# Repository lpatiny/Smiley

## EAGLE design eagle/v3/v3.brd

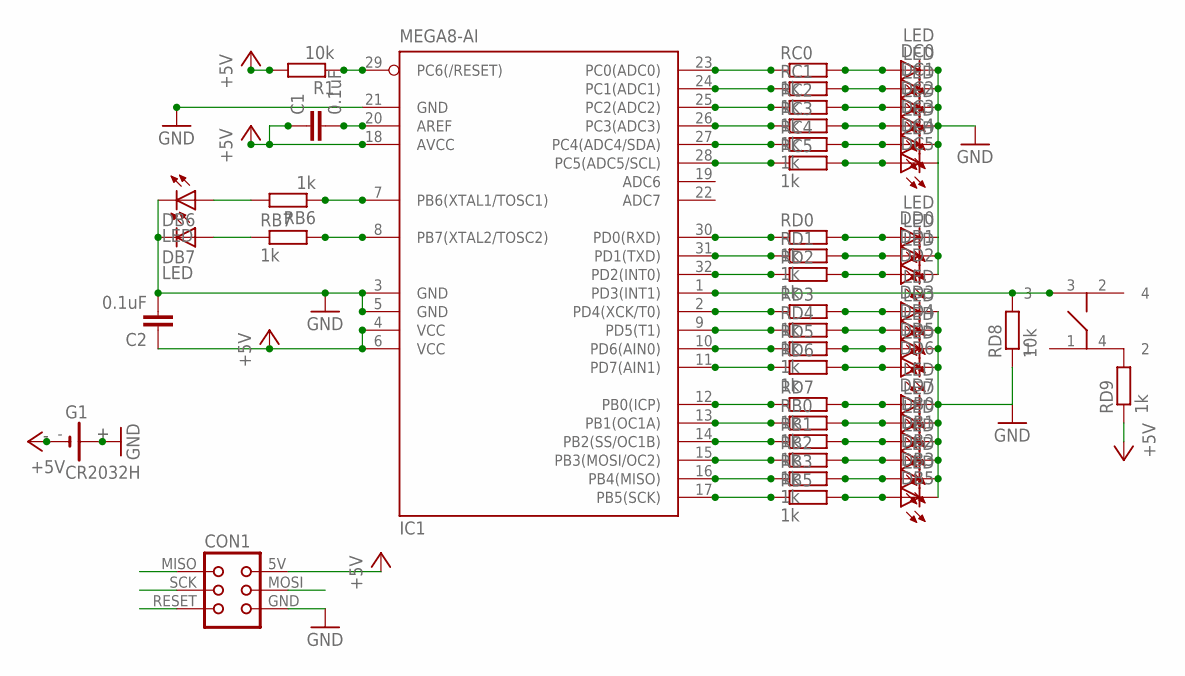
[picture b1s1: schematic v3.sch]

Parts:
C1, C2: 0.1uF; C0402
CON1: TINYISPT; TC2030-MCP-NL
DB0, DB1, DB2, DB3, DB5, DB6, DB7: LED; D0402
DC0, DC1, DC2, DC3, DC4, DC5: LED; D0402
DD0, DD1, DD2, DD3, DD4, DD5, DD6, DD7: LED; D0402
G1: CR2032H
IC1: MEGA8-AI; TQFP32-08
R1: 10k; R0402
RB0, RB1, RB2, RB3, RB5, RB6, RB7: 1k; R0402
RC0, RC1, RC2, RC3, RC4, RC5: 1k; R0402
RD0, RD1, RD2, RD3, RD4, RD5, RD6, RD7, RD9: 1k; R0402
RD8: 10k; R0402
U$2: TEUCH4MM

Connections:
+5V: C1.1, C2.1, CON1.5V (VCC), G1.-, IC1.4 (VCC), IC1.6 (VCC), IC1.18 (AVCC), R1.2, RD9.1
GND: C2.2, CON1.GND, DB0.C, DB1.C, DB2.C, DB3.C, DB5.C, DB6.C, DB7.C, DC0.C, DC1.C, DC2.C, DC3.C, DC4.C, DC5.C, DD0.C, DD1.C, DD2.C, DD3.C, DD4.C, DD5.C, DD6.C, DD7.C, G1.+, IC1.3 (GND), IC1.5 (GND), IC1.21 (GND), RD8.1
MISO: CON1.MISO
MOSI: CON1.MOSI
unnamed: IC1.7 (PB6(XTAL1/TOSC1)), RB6.1
unnamed: IC1.24 (PC1(ADC1)), RC1.1
unnamed: IC1.23 (PC0(ADC0)), RC0.1
unnamed: C1.2, IC1.20 (AREF)
unnamed: IC1.26 (PC3(ADC3)), RC3.1
unnamed: IC1.25 (PC2(ADC2)), RC2.1
unnamed: IC1.27 (PC4(ADC4/SDA)), RC4.1
unnamed: IC1.28 (PC5(ADC5/SCL)), RC5.1
unnamed: IC1.30 (PD0(RXD)), RD0.1
unnamed: IC1.31 (PD1(TXD)), RD1.1
unnamed: IC1.17 (PB5(SCK)), RB5.1
unnamed: IC1.32 (PD2(INT0)), RD2.1
unnamed: IC1.16 (PB4(MISO)), RB3.1
unnamed: IC1.15 (PB3(MOSI/OC2)), RB2.1
unnamed: IC1.14 (PB2(SS/OC1B)), RB1.1
unnamed: IC1.13 (PB1(OC1A)), RB0.1
unnamed: IC1.12 (PB0(ICP)), RD7.1
unnamed: IC1.11 (PD7(AIN1)), RD6.1
unnamed: IC1.10 (PD6(AIN0)), RD5.1
unnamed: IC1.9 (PD5(T1)), RD4.1
unnamed: IC1.8 (PB7(XTAL2/TOSC2)), RB7.2
unnamed: U$2.1, U$2.4 (2)
unnamed: U$2.2 (4), U$2.3
unnamed: DB7.A, RB7.1
unnamed: DC0.A, RC0.2
unnamed: DC1.A, RC1.2
unnamed: DC2.A, RC2.2
unnamed: DC3.A, RC3.2
unnamed: DC4.A, RC4.2
unnamed: DC5.A, RC5.2
unnamed: DD0.A, RD0.2
unnamed: DD1.A, RD1.2
unnamed: DD2.A, RD2.2
unnamed: DD3.A, RD3.2
unnamed: DD4.A, RD4.2
unnamed: DD5.A, RD5.2
unnamed: DD6.A, RD6.2
unnamed: DD7.A, RD7.2
unnamed: DB0.A, RB0.2
unnamed: DB1.A, RB1.2
unnamed: DB2.A, RB2.2
unnamed: DB3.A, RB3.2
unnamed: IC1.2 (PD4(XCK/T0)), RD3.1
unnamed: DB6.A, RB6.2
unnamed: IC1.1 (PD3(INT1)), RD8.2
unnamed: DB5.A, RB5.2
RESET: CON1.RESET, IC1.29 (PC6(/RESET)), R1.1
SCK: CON1.SCK

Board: 2 copper layers, 51 parts (26 on the bottom side), 49 nets, no tracks yet.

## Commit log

2013-01-05 First draft
2013-01-05 ignore
2013-01-06 Second draft
2013-01-06 Version V1
2013-01-06 Update hierarchy
2014-02-02 Renove DS store
2014-02-02 Update pico smiley
2014-02-02 Updae nano
2015-01-04 Nouvelle version 0402 !!!!!!!!!!!!!
2015-03-22 Update smiley
2015-03-22 Update library
2015-03-29 Add Pro

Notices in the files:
parts and their libraries:
lpatiny: ©2009 ROFA.cz - modified and updated by Robert Darlington ‹rdarlington@gmail.com›
